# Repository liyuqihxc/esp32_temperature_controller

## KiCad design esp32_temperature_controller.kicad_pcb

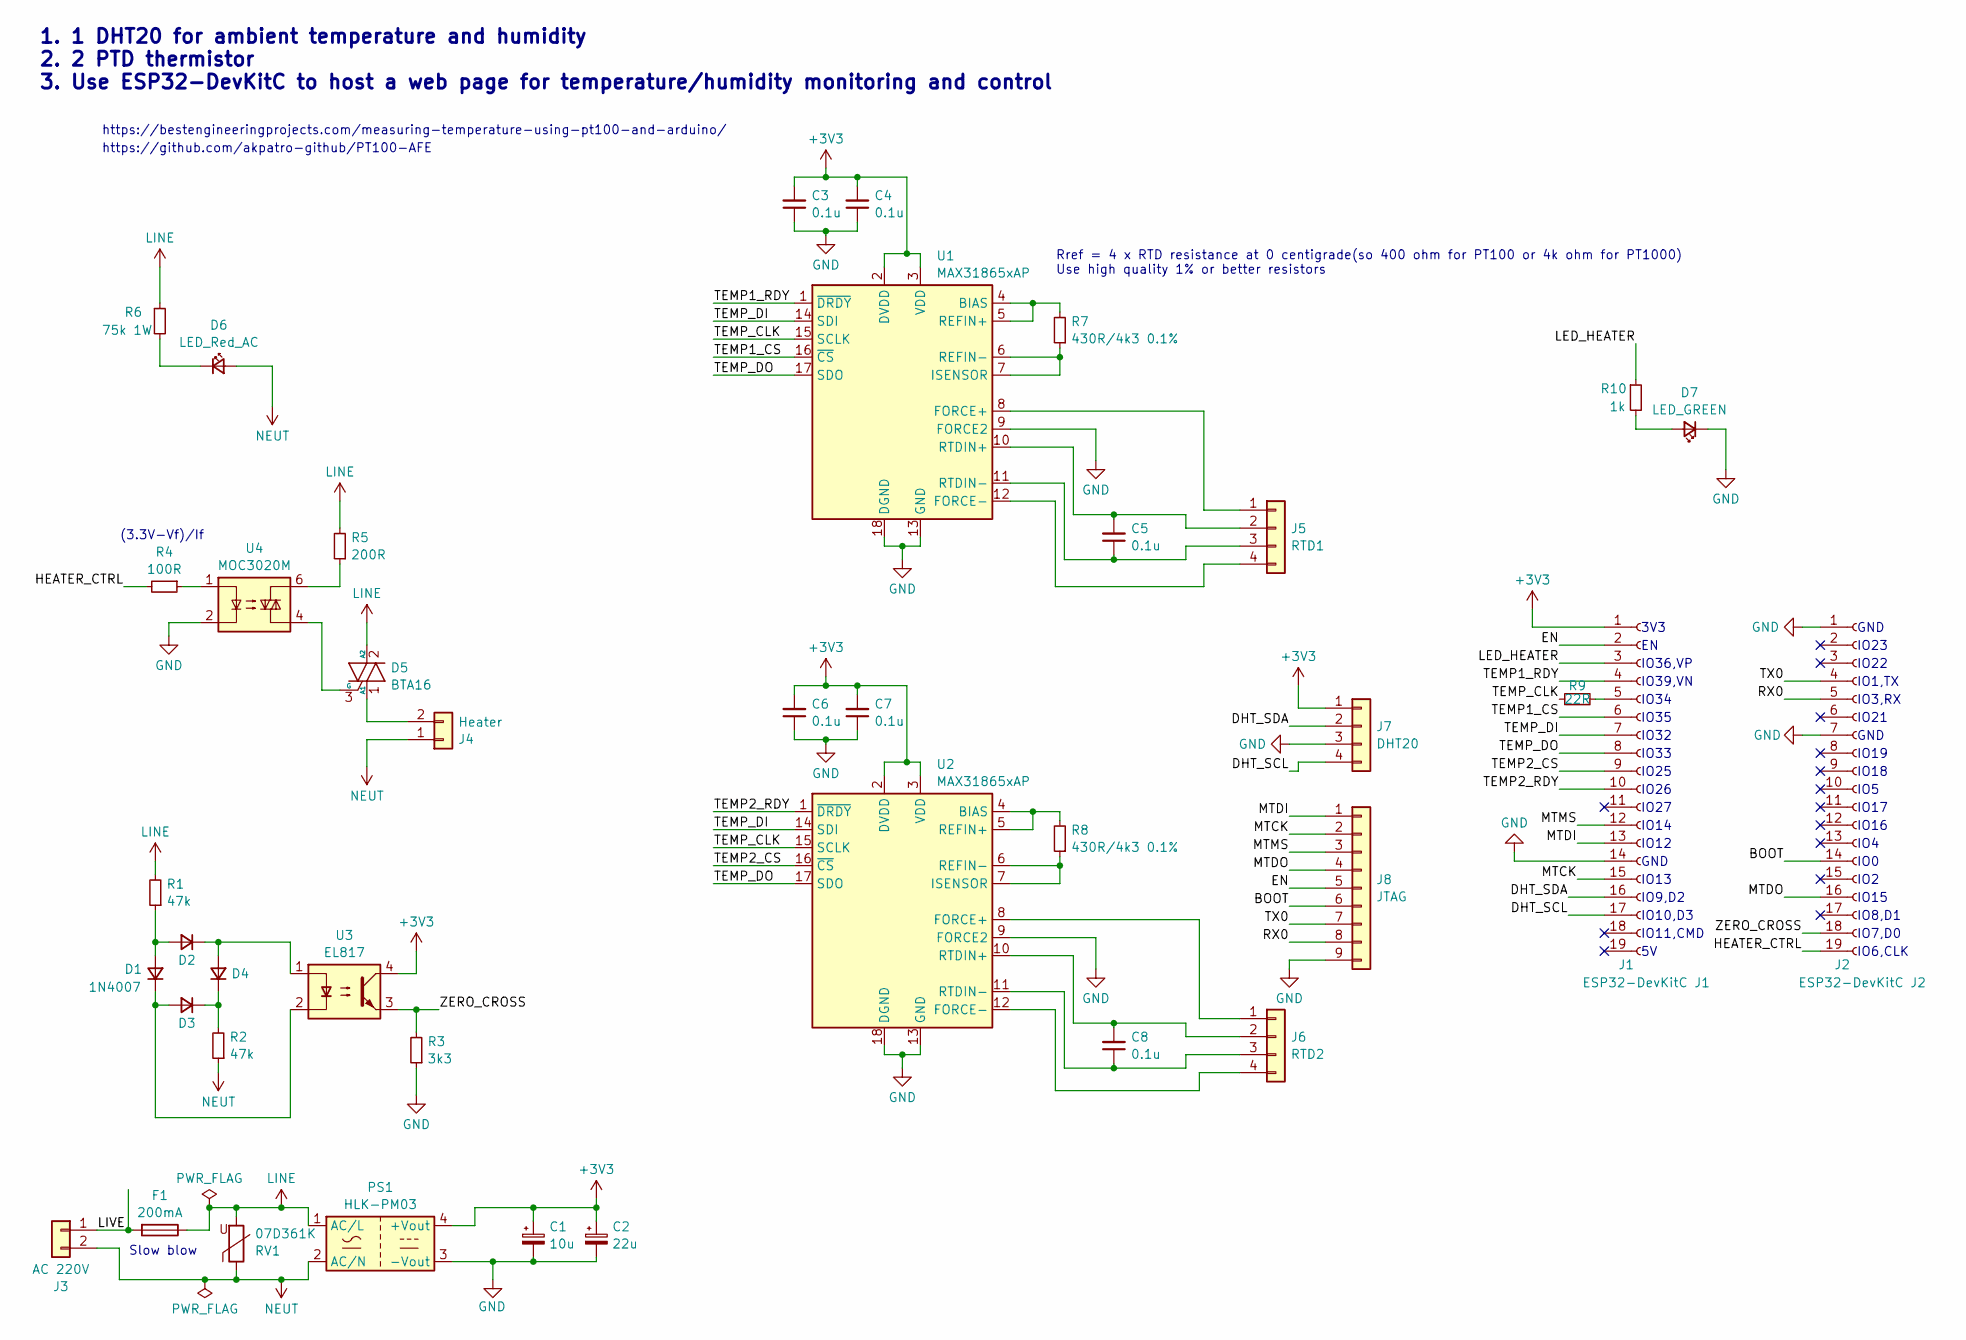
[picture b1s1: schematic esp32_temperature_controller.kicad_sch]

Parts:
C1: 10u; CP_Elec_4x5.4; PartNum C4747969
C2: 22u; CP_Elec_4x5.4; PartNum C335975
C3, C4, C5, C6, C7, C8: 0.1u; C_0402_1005Metric_Pad0.74x0.62mm_HandSolder
D1, D2, D3, D4: 1N4007; D_SMA; PartNum C727081
D5: BTA16; TO-220-3_Vertical; PartNum C7437431
D6: LED_Red_AC; LED_0603_1608Metric_Pad1.05x0.95mm_HandSolder; PartNum C965799
D7: LED_GREEN; LED_0603_1608Metric_Pad1.05x0.95mm_HandSolder; PartNum C965799
F1: 200mA; Fuseholder_Clip-5x20mm_Littelfuse_100_Inline_P20.50x4.60mm_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; PartNum C3130
J1: ESP32-DevKitC J1; PinSocket_1x19_P2.54mm_Vertical
J2: ESP32-DevKitC J2; PinSocket_1x19_P2.54mm_Vertical
J3: AC 220V; PhoenixContact_MCV_1,5_2-G-5.08_1x02_P5.08mm_Vertical; PartNum C8445
J4: Heater; PhoenixContact_MCV_1,5_2-G-5.08_1x02_P5.08mm_Vertical; PartNum C8445
J5: RTD1; JST_XH_B4B-XH-A_1x04_P2.50mm_Vertical
J6: RTD2; JST_XH_B4B-XH-A_1x04_P2.50mm_Vertical
J7: DHT20; R_Array_SIP4; PartNum C144394
J8: JTAG; PinHeader_1x09_P2.54mm_Vertical; PartNum C144394
PS1: HLK-PM03; Converter_ACDC_HiLink_HLK-5Mxx
R1, R2: 47k; R_0603_1608Metric_Pad0.98x0.95mm_HandSolder
R3: 3k3; R_0402_1005Metric_Pad0.72x0.64mm_HandSolder
R4: 100R; R_0402_1005Metric_Pad0.72x0.64mm_HandSolder
R5: 200R; R_2512_6332Metric
R6: 75k 1W; R_2512_6332Metric; PartNum C2907588
R7, R8: 430R/4k3 0.1%; R_0402_1005Metric_Pad0.72x0.64mm_HandSolder
R9: 22R; R_0402_1005Metric_Pad0.72x0.64mm_HandSolder
R10: 1k; R_0402_1005Metric_Pad0.72x0.64mm_HandSolder
RV1: 07D361K; RV_Disc_D7mm_W4.3mm_P5mm; PartNum C317762
U1, U2: MAX31865xAP; SSOP-20_5.3x7.2mm_P0.65mm
U3: EL817; DIP-4_W7.62mm; PartNum C181889
U4: MOC3020M; DIP-6_W7.62mm; PartNum C5158042

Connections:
+3V3: C1.1, C2.1, C3.2, C4.2, C6.2, C7.2, J1.1, J7.1, PS1.4 (+Vout), U1.2 (DVDD), U1.3 (VDD), U2.2 (DVDD), U2.3 (VDD), U3.4
/BOOT: J2.14, J8.6
/DHT_SCL: J1.17, J7.4
/DHT_SDA: J1.16, J7.2
/EN: J1.2, J8.5
/HEATER_CTRL: J2.19, R4.2
/LED_HEATER: J1.3, R10.1
/LIVE: F1.2, J3.1
/MTCK: J1.15, J8.2
/MTDI: J1.13, J8.1
/MTDO: J2.16, J8.4
/MTMS: J1.12, J8.3
/RX0: J2.5, J8.8
/TEMP1_CS: J1.6, U1.16 (~CS)
/TEMP1_RDY: J1.4, U1.1 (~DRDY)
/TEMP2_CS: J1.9, U2.16 (~CS)
/TEMP2_RDY: J1.10, U2.1 (~DRDY)
/TEMP_CLK: R9.1, U1.15 (SCLK), U2.15 (SCLK)
/TEMP_DI: J1.7, U1.14 (SDI), U2.14 (SDI)
/TEMP_DO: J1.8, U1.17 (SDO), U2.17 (SDO)
/TX0: J2.4, J8.7
/ZERO_CROSS: J2.18, R3.2, U3.3
GND: C1.2, C2.2, C3.1, C4.1, C6.1, C7.1, D7.1 (K), J1.14, J2.1, J2.7, J7.3, J8.9, PS1.3 (-Vout), R3.1, U1.9 (FORCE2), U1.13 (GND), U1.18 (DGND), U1.19 (GND), U2.9 (FORCE2), U2.13 (GND), U2.18 (DGND), U2.19 (GND), U4.2
LINE: D5.2 (A2), F1.1, PS1.1 (AC/L), R1.2, R5.2, R6.1, RV1.2
NEUT: D6.2 (A), J3.2, J4.1, PS1.2 (AC/N), R2.1, RV1.1
unnamed: D1.2 (A), D2.2 (A), R1.1
unnamed: D1.1 (K), D3.2 (A), U3.2
unnamed: D2.1 (K), D4.2 (A), U3.1
unnamed: D3.1 (K), D4.1 (K), R2.2
unnamed: D5.1 (A1), J4.2
unnamed: D5.3 (G), U4.4
unnamed: D6.1 (K), R6.2
unnamed: D7.2 (A), R10.2
unnamed: J1.5, R9.2
unnamed: J5.1, U1.8 (FORCE+)
unnamed: C5.2, J5.2, U1.10 (RTDIN+)
unnamed: C5.1, J5.3, U1.11 (RTDIN-)
unnamed: J5.4, U1.12 (FORCE-)
unnamed: J6.1, U2.8 (FORCE+)
unnamed: C8.2, J6.2, U2.10 (RTDIN+)
unnamed: C8.1, J6.3, U2.11 (RTDIN-)
unnamed: J6.4, U2.12 (FORCE-)
unnamed: R4.1, U4.1
unnamed: R5.1, U4.6
unnamed: R7.2, U1.4 (BIAS), U1.5 (REFIN+)
unnamed: R7.1, U1.6 (REFIN-), U1.7 (ISENSOR)
unnamed: R8.2, U2.4 (BIAS), U2.5 (REFIN+)
unnamed: R8.1, U2.6 (REFIN-), U2.7 (ISENSOR)

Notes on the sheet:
IO3,RX
(3.3V-Vf)/If
IO34
IO36,VP
IO8,D1
https://github.com/akpatro-github/PT100-AFE
IO9,D2
IO26
IO15
GND
IO17
IO10,D3
IO27
IO33
IO18
IO23
IO11,CMD
IO12
IO14
IO19
IO35
IO32
https://bestengineeringprojects.com/measuring-temperature-using-pt100-and-arduino/
Rref = 4 x RTD resistance at 0 centigrade(so 400 ohm for PT100 or 4k ohm for PT1000) Use high quality 1% or better resistors
IO1,TX
Slow blow
IO39,VN
IO5
IO16
3V3
IO0
IO4
IO6,CLK
IO2
IO22
IO21
IO13
IO7,D0
IO25
1. 1 DHT20 for ambient temperature and humidity 2. 2 PTD thermistor 3. Use ESP32-DevKitC to host a web page for temperature/humidity monitoring and control

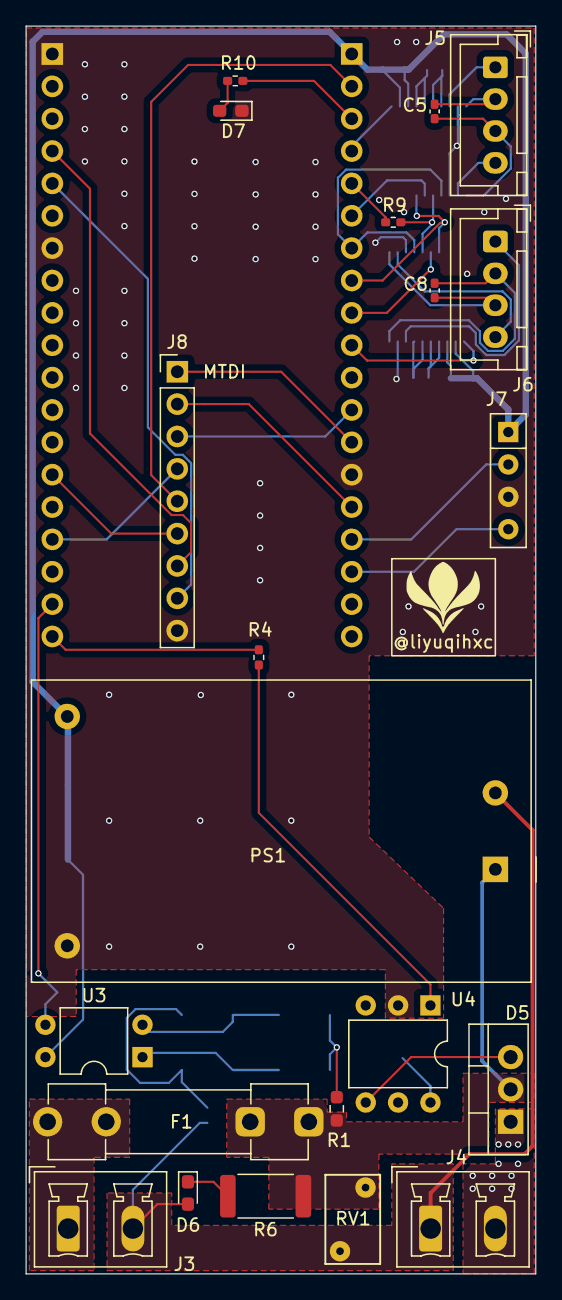
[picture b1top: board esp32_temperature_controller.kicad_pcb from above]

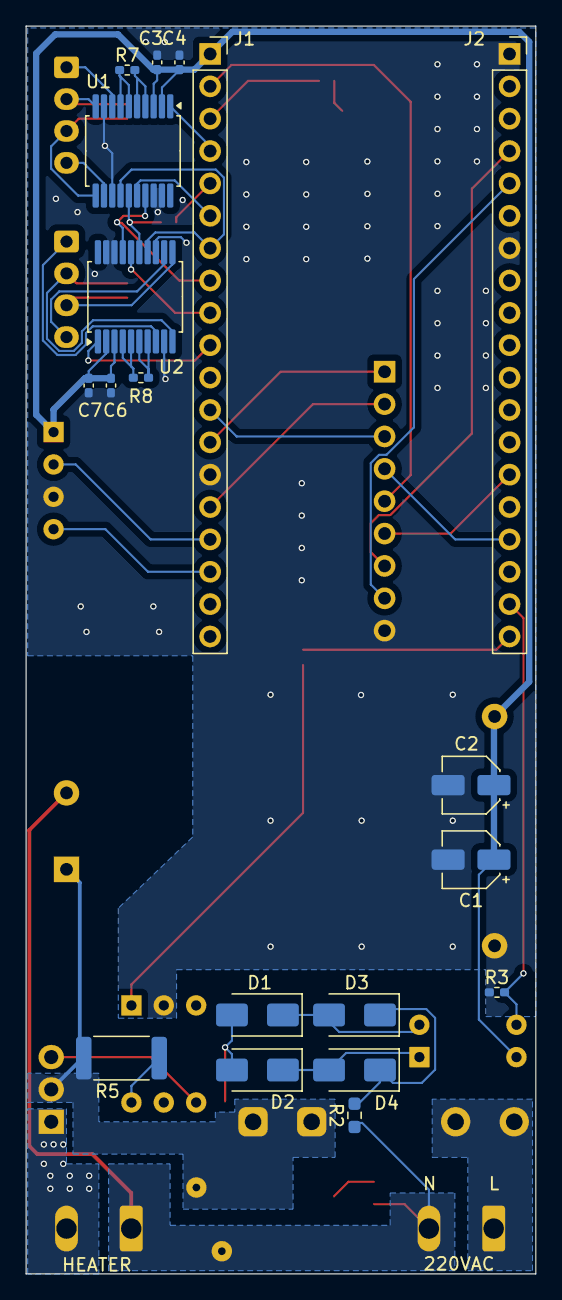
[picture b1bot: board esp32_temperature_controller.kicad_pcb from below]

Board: 2 copper layers, 40.0 x 97.9 mm, 40 parts (19 on the bottom side), 48 nets.

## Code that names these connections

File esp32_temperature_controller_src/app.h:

#ifndef _APP_H_
#define _APP_H_

#include <Preferences.h>

#define _DEBUG

#ifdef _DEBUG
#define SERIAL_WRITE(s) Serial.print(s)
#define SERIAL_WRITE_LINE(s) Serial.println(s)
#else
#define SERIAL_WRITE(s)
#define SERIAL_WRITE_LINE(s)
#endif

#define PIN_DHT20_SCL         0
#define PIN_DHT20_SDA         2

#define PIN_TEMP1_CS          3
#define PIN_TEMP2_CS          5
#define PIN_TEMP_DI           1
#define PIN_TEMP_DO           19
#define PIN_TEMP_CLK          21
#define PIN_TEMP1_RDY         22
#define PIN_TEMP2_RDY         16

#define PIN_ZERO_CROSS        10
#define PIN_HEATER_CTRL       11
#define PIN_LED_HEATING_STATE 23

const char *const PREF_APP_NAME = "name";
const char *const PREF_HEATER_MODE = "mode";
const char *const PREF_HEATER_VALUE = "value";
const char *const PREF_WIFI_SSID = "ssid";
const char *const PREF_WIFI_PASSWORD = "password";
const char *const PREF_ENABLE_MQTT_CLIENT = "mqtt_on";
const char *const PREF_MQTT_BROKER = "broker";
const char *const PREF_MQTT_TOPIC = "topic";

// Default AP credentials
const char *const default_ap_ssid = "ESP32_TEMP_CTRL";
const char *const default_ap_password = "12345678";

extern Preferences preferences;

#endif

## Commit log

2024-02-01 change the drill hole to 1.6mm for the ac socket foot print
2024-02-02 implement controller initial setup configuration
2024-02-29 add debug port; change max31865 to ssop-20
2024-02-29 switch to esp idf
